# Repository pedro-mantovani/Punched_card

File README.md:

# Punched Card Simulator

> 🇺🇸 English | [🇧🇷 Versão em Português](#simulador-de-cartoes-perfurados)

## Overview

This project simulates how a punched card works using slide switches to represent the lines (or holes) of the card. The selected pattern is interpreted and displayed on an LCD screen.

It was designed for educational purposes, allowing students to experience the high effort once required to program using punched cards, and to provide a more tangible model of how this process worked in early computing.

### Images

---

## How It Works

Each switch is connected to a digital pin on the Arduino Nano. The "HIGH" position represents a hole in the punched card. The combination of holes is processed as a binary number by the Arduino, which then sends the corresponding symbol to the display, based on the IBM 029 model ([reference](https://www.masswerk.at/keypunch/)).

The code logic consists of multiple switch-case blocks grouped similarly to how manual keypunch machines were organized. Even though a single switch-case block could do the job, the structure was chosen to emulate how the first three rows worked like a "shift", changing the way the remaining rows were interpreted.

When the push button is pressed, the cursor moves forward, preserving the previous character and allowing up to 16 characters to be typed.

To clear the display, you need to press the Arduino's reset button. This restarts the program and helps keep the display logic clean, avoiding unexpected behavior from prolonged use.

### Other Features:
- For better visibility, the current character alternates with a solid block, indicating the cursor's position.
- The first row of the LCD shows a binary representation of the current switches configuration.

**Character Mapping:**

---

## Components Used

| Quantity | Component         | Model            
|----------|-------------------|------------------
| 1        | LCD Display       | 16x2 HD44780     
| 1        | I2C Module        | PCF8574          
| 1        | Arduino Nano      | Atmega328 CH340  
| 1        | Push Button       | 6x6x5 mm         
| 12       | Slide Switches    | SS12D00G4        
| 1        | Header (M-F)      | 40 pins          
| 1        | Phenolic Board    | 10x10 cm         

---

# Usage / Assembly Instructions

You can test the circuit online using [Tinkercad](https://www.tinkercad.com/things/hIHtu1BwrTN-simulador-de-cartao-perfurado)

It works just like the physical prototype, although the circuit timing has been adjusted for better visualization in the simulator, since Tinkercad's execution speed differs from real time.

### Physical Assembly

It's recommended to test the project on a breadboard first.  
However, for consistent usage, a printed circuit board (PCB) is essential — the number of wires involved can lead to unreliable connections on a breadboard. Also, the switches are small and may detach easily when manipulated.

📹 [Video of the prototype](/Imagens%20e%20vídeos/protótipo.mp4)

For PCB assembly, you can:
- Use the provided [PDF](/Códigos%20e%20arquivos/trilhas.pdf) file for ready-to-print traces,
- Or customize the schematic and board files using EAGLE.

---

## Circuit

[Circuit file (BRD)](/Códigos%20e%20arquivos/simulador.brd)

## Schematic

[Schematic file](/Códigos%20e%20arquivos/simulador.sch)

---

## 💡 Tips

- Remember to adjust the LCD contrast.
- You can customize the pin configuration.
- All the timing can be changed to suit your needs.
- If you are making a PCB, remember to solder both sides. To make this job easier, you can use the [one-side version](/Imagens%20e%20vídeos/one-side.png) and manually complete the 11 remaining connections.

---

## Authors:

This project was developed as part of the Electronics discipline by:

**Pedro Otavio Mantovani**

**Mariane Ferreira dos Santos**

---

# Simulador de Cartoes Perfurados

> 🇧🇷 Português | [🇺🇸 English Version](#punched-card-simulator)

## Visão Geral

Este projeto simula o funcionamento de um cartão perfurado usando interruptores para representar as linhas de um cartão. O padrão selecionado é interpretado e exibido em um display LCD.

Ele foi projetado para fins pedagógicos para que os estudantes possam experimentar o esforço hercúleo necessário para programar com cartões perfurados e tenham um modelo mais palpável de como esse processo funcionava.

### Imagens e vídeos

## Como Funciona
Cada interruptor está ligado a um pino do Arduino Nano, a posição "ligado" representa um furo no cartão, a combinação de furos é processada como um número binário pelo Arduino, que envia para o display o símbolo correspondente conforme o padrão IBM 029 ([referência](https://www.masswerk.at/keypunch/)).

A lógica do código consiste em vários switch cases agrupados de maneira análoga ao agrupamento das perfuradoras manuais. O código também funcionaria com um switch case único, mas quis trazer para o código essa noção de que as três linhas iniciais funcionam como um "shift" que altera a forma como as linhas principais são interpretadas.

Quando o botão é pressionado o cursor é movido para frente preservando o caractere na posicão anterior e permitindo a escrita de até 16 caracteres.

Para limpar o display é necessário pressionar o botão de reset do Arduino, assim o programa é reiniciado, mantendo o código sempre "limpo", evitando bugs inesperados devido ao uso contínuo.

**Outras funcionalidades:**

Para melhor visibilidade o caractere atual se alterna com um bloco sólido indicando a posição do cursor;

A primeira linha mostra uma correspondência binária da posição atual dos interruptores.

Padrão utilizado:

## Materiais utilizados
| Quantidade |  Componente  | Modelo |  Valor (Unidade)  |
|------------|--------------|--------|---------|
| 1 | Display LCD | 16x2 HD44780 | R$13,90 |
| 1 | Módulo I2C | PCF8574 | R$12,00 |
| 1 | Arduino Nano | Atmega328 Ch340 | R$34,90 |
| 1 | Push Button | 6x6x5mm | R$0,15 |
| 12 | Interruptor | SS12D00G4 | R$0,30 |
| 1 | Header macho-fêmea | 40 pinos | R$4,00 |
| 1 | Placa fenolite | 10x10cm | R$8,45 |
|**Total**|||**R$77,00**|

# Instruções de uso / Construção
É possível testar o cicuito via internet pelo [Tinkercad](https://www.tinkercad.com/things/hIHtu1BwrTN-simulador-de-cartao-perfurado)

Funciona exatamente como o protótipo, porém o timing do circuito está alterado para melhor visualização no programa visto que o tempo do simulador não corresponde à realidade.   
  
Para construção física, é recomendado testar antes em uma protoboard, mas para uso é indispensável o circuito impresso pois a quantidade de fios é enorme, o que faz com que o circuito tenha muito mal contato, fora que os interruptores são muito pequenos sendo mais fácil tirá-los da protoboard que mudar suas posições.

[Vídeo do projeto na protoboard](/Imagens%20e%20vídeos/protótipo.mp4)

Para a construção em circuito impresso é possível utilizar o [PDF](/Códigos%20e%20arquivos/trilhas.pdf) pronto das trilhas ou fazer alterações no arquivo esquemático e/ou no circuito usando o EAGLE.

## Circuito

[Arquivo do circuito](/Códigos%20e%20arquivos/simulador.brd)

## Esquemático

[Arquivo do esquemático](/Códigos%20e%20arquivos/simulador.sch)

### 💡 Dicas

- Lembre-se de ajustar o contraste do display (caso contrário, o backlight acenderá, mas nenhuma letra será exibida).
- A leitura do botão, o tempo de piscar do cursor e a pinagem podem ser facilmente alterados dentro da função `void setup()`.
- Lembre-se de soldar a placa dos dois lados, ou usar a [versão de um lado só](/Imagens%20e%20vídeos/one-side.png) e fazer manualmente as dez ligações restantes.

### Autores
Esse trabalho faz parte da disciplina de Eletrônica, grupo do projeto:

**Pedro Otavio Mantovani**

**Mariane Ferreira dos Santos**

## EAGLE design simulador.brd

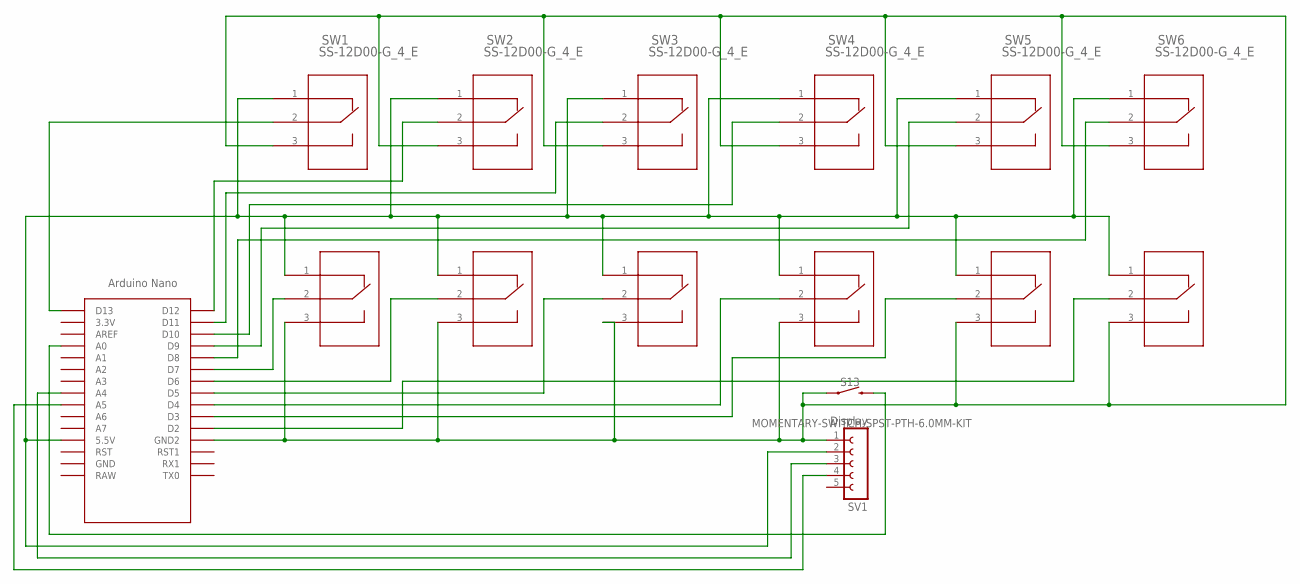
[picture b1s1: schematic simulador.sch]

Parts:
S13: MOMENTARY-SWITCH-SPST-PTH-6.0MM-KIT; TACTILE_SWITCH_PTH_6.0MM_KIT
SV1: Display; FE05-1
SW1, SW2, SW3, SW4, SW5, SW6, SW7, SW8, SW9, SW10, SW11, SW12: SS-12D00-G_4_E; 1P2T_SS-12D00_CNK
U$1: NANO

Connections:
unnamed: SV1.2, SW1.1, SW2.1, SW3.1, SW4.1, SW5.1, SW6.1, SW7.1, SW8.1, SW9.1, SW10.1, SW11.1, SW12.1, U$1.5V (5.5V)
unnamed: S13.3 (2), U$1.A0
unnamed: SV1.3, U$1.A4
unnamed: SV1.4, U$1.A5
unnamed: S13.1, SV1.1, SW1.3, SW2.3, SW3.3, SW4.3, SW5.3, SW6.3, SW7.3, SW8.3, SW9.3, SW10.3, SW11.3, SW12.3, U$1.GND1 (GND2)
unnamed: SW1.2, U$1.D13
unnamed: SW2.2, U$1.D12
unnamed: SW3.2, U$1.D11
unnamed: SW7.2, U$1.D7
unnamed: SW4.2, U$1.D10
unnamed: SW5.2, U$1.D9
unnamed: SW6.2, U$1.D8
unnamed: SW8.2, U$1.D6
unnamed: SW9.2, U$1.D5
unnamed: SW10.2, U$1.D4
unnamed: SW11.2, U$1.D3
unnamed: SW12.2, U$1.D2

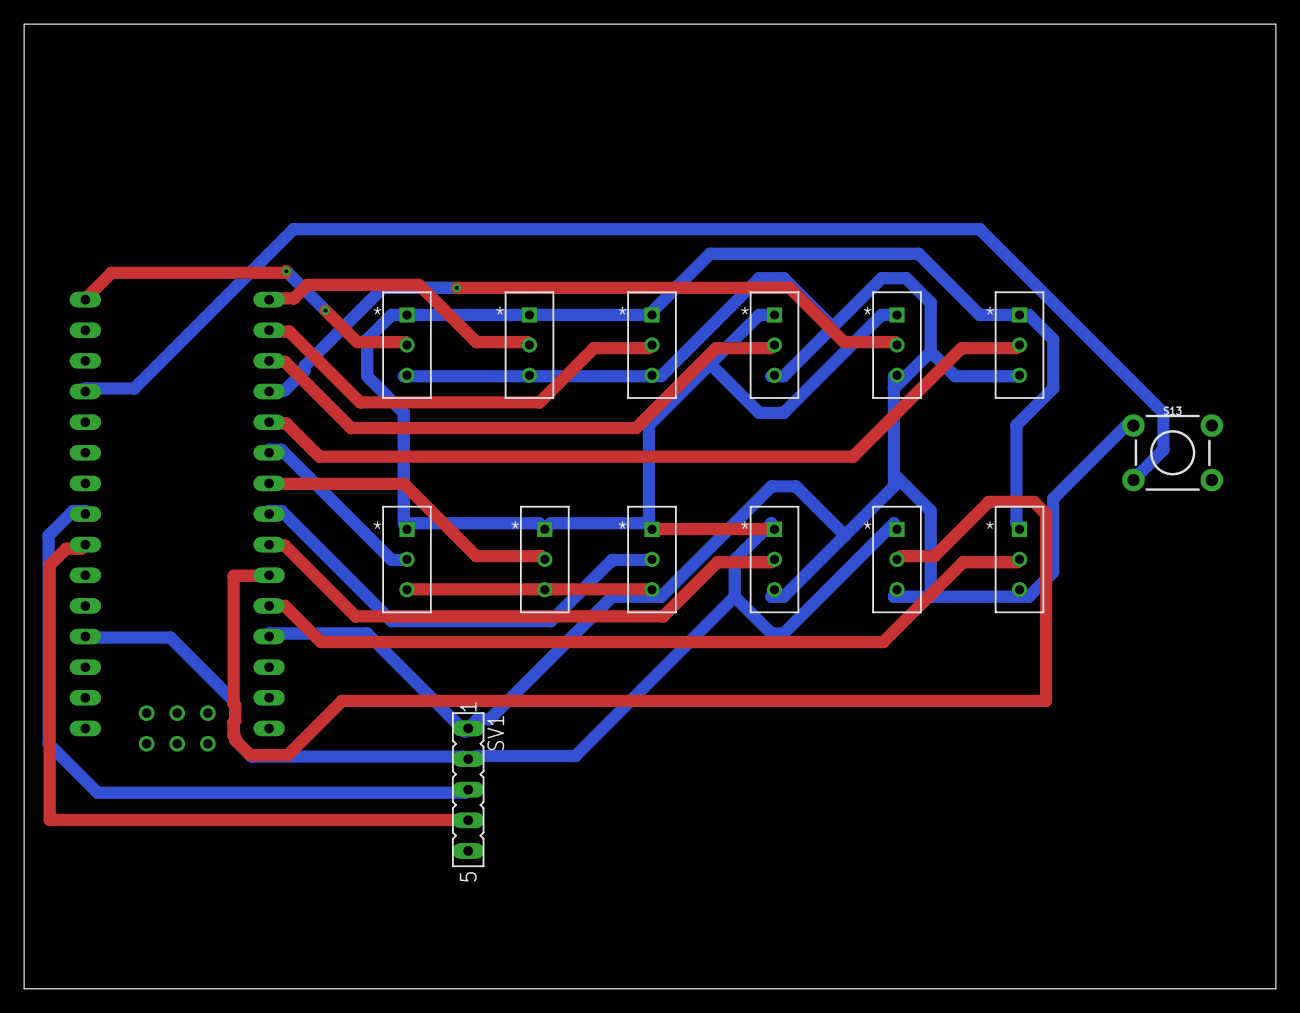
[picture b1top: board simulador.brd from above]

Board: 2 copper layers, 103.8 x 80.0 mm, 15 parts (0 on the bottom side), 17 nets.

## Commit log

2025-06-29 Version 1.0
2025-06-29 Create LICENSE
2025-06-30 README
2025-07-03 Atualizações README

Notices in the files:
parts and their libraries:
SparkFun-Switches: Licensing: Creative Commons ShareAlike 4.0 International - https://creativecommons.org/licenses/by-sa/4.0
untitled: COPYRIGHT: Copyright (C) 2025 Ultra Librarian. All rights reserved.
